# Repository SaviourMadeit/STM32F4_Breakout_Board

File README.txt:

# STM32F405RGT6_Breakout_Board

This repository contains the design files, schematics, and documentation for the STM32F4 Breakout Board.
This breakout board is designed to simplify the development process by providing easy access to essential 
features of the STM32F4 microcontroller, including voltage regulation, communication protocols, debugging interfaces, and indicator LEDs.

## Features

- 3.3V Voltage Regulator: The breakout board includes a 3.3V voltage regulator to ensure a stable power supply for 
                              connected peripherals and the STM32F4 microcontroller.

- 3.3V Power Pin: Provides a convenient 3.3V power pin for external components or modules that require a regulated power supply.

- LED Indicator: An indicator LED for visual feedback or status indication during development.

- Communication Protocols:

  - SPI: Headers and connectors for Serial Peripheral Interface (SPI) communication.
  - UART: Interface for Universal Asynchronous Receiver-Transmitter (UART) communication.
  - I2C: Connectors for Inter-Integrated Circuit (I2C) communication.

- Serial Wire Debugger Pins: Dedicated pins for Serial Wire Debugging (SWD) to assist in code development and debugging processes.

## Contents

- Schematics: Contains the schematic, and footprint files detailing the board's layout and connections.
- Gerber_Files: Gerber files for PCB fabrication and Assembly.
- Documentation: Additional documentation, usage guides, and pinout details.
- Examples: Sample code examples demonstrating the use of different communication protocols with the breakout board.

## Usage

1. Hardware Setup: Connect the necessary peripherals or components to the designated headers and pins on the breakout board.
   
2. Power Supply: Ensure a stable power supply of max 5v is provided to the breakout board through the appropriate power input VIN pin.

3. Communication: Utilize the provided headers and connectors to establish communication using SPI, UART, or I2C protocols.

4. Debugging: Utilize the Serial Wire Debugger pins for development and debugging of code. Refer to the documentation for more details on debugging setup.

## Contributing

Contributions to enhance the breakout board design, improve documentation, or add new features are welcome. 
Please follow the guidelines outlined in the `CONTRIBUTING.md` file.

## License

This project is licensed under the [MIT License](LICENSE).

## Acknowledgments

Special thanks to the Phil's Lab,STM32F4 community and contributors for their support and resources that aided in the development of this breakout board.

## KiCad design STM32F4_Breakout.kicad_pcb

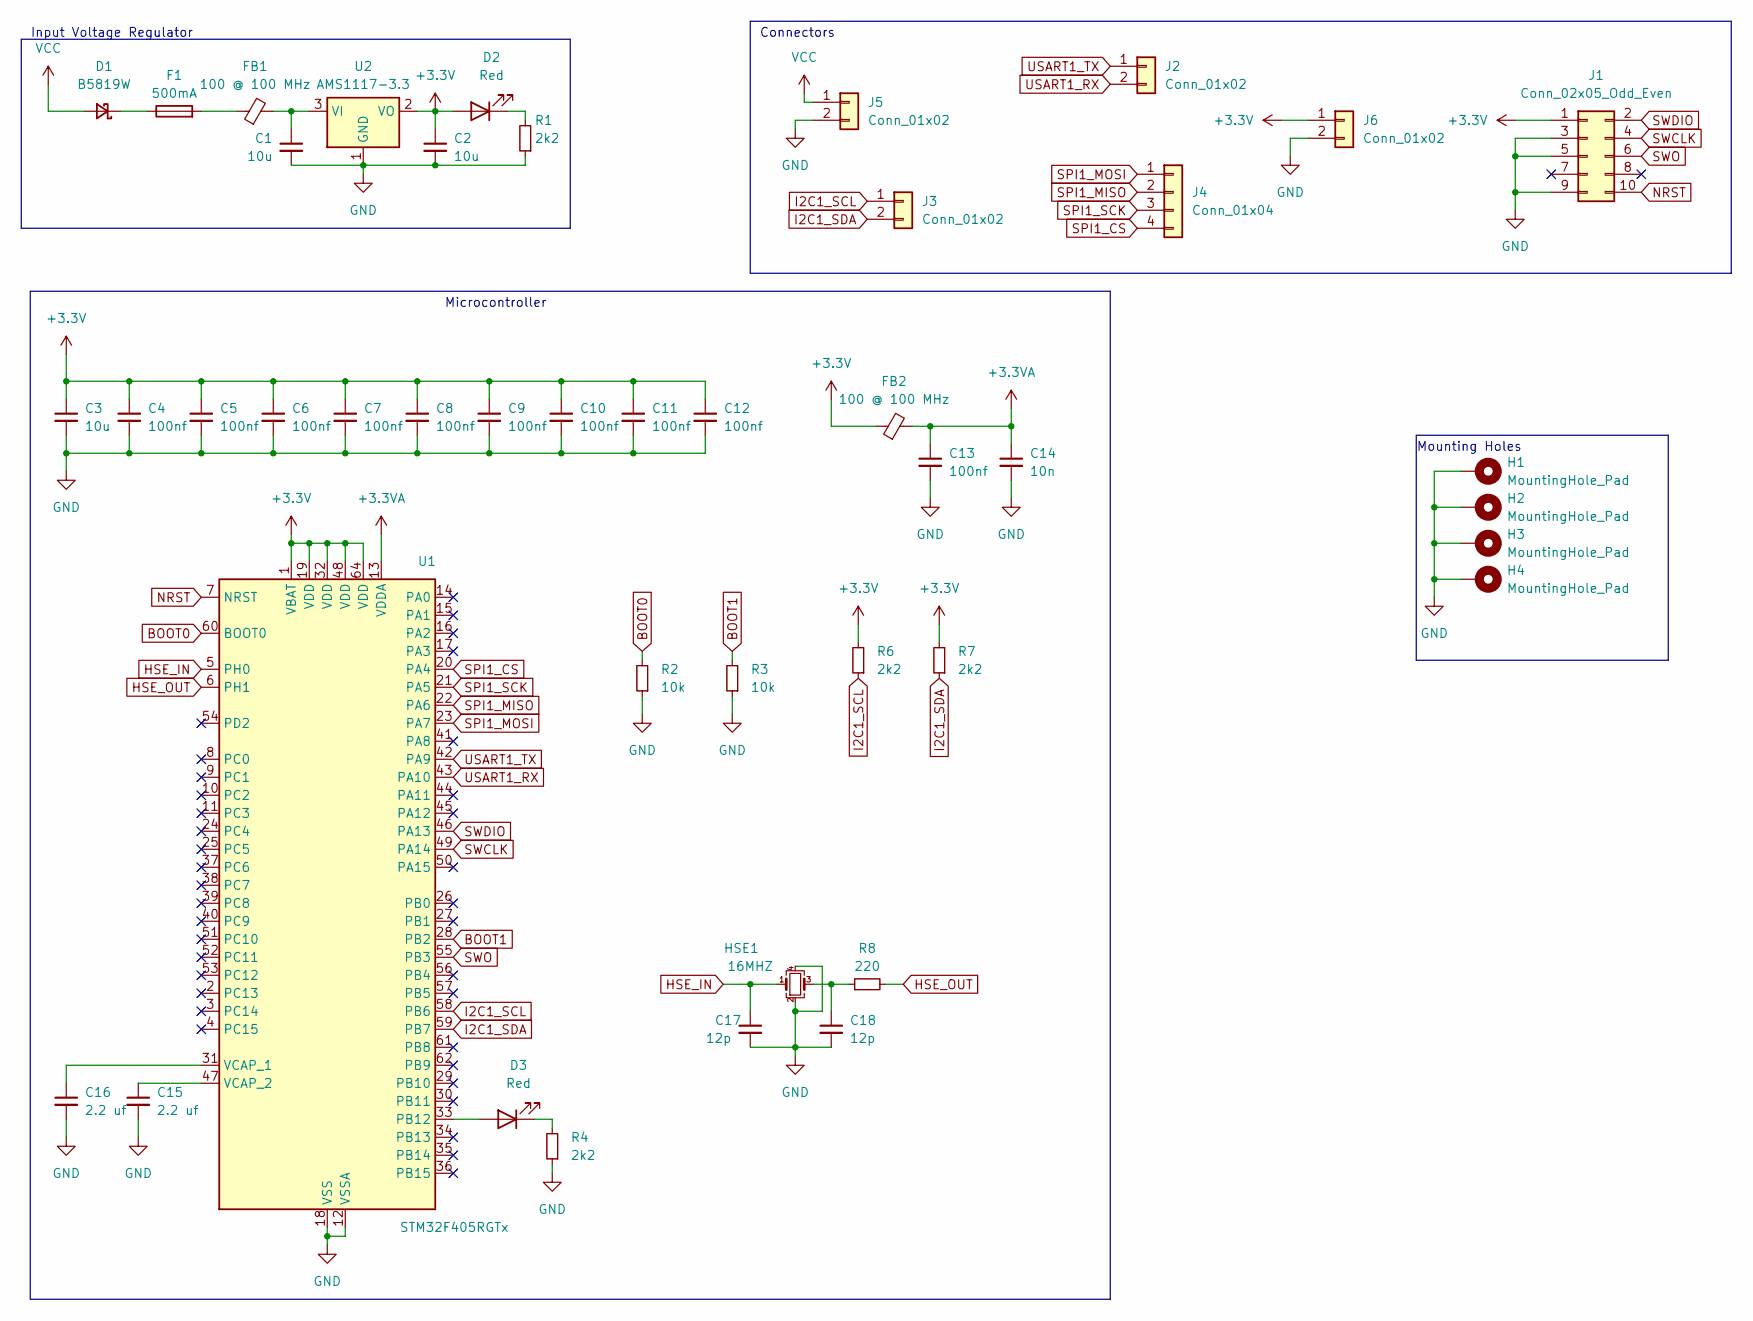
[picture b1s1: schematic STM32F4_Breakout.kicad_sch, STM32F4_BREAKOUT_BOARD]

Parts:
C1, C2: 10u; C_0805_2012Metric
C3: 10u; C_0603_1608Metric
C4, C5, C6, C7, C8, C9, C10, C11, C12, C13: 100nf; C_0402_1005Metric
C14: 10n; C_0402_1005Metric
C15, C16: 2.2 uf; C_0603_1608Metric
C17, C18: 12p; C_0402_1005Metric
D1: B5819W; D_SOD-123
D2, D3: Red; LED_0603_1608Metric
F1: 500mA; Fuse_0603_1608Metric
FB1, FB2: 100 @ 100 MHz; L_0805_2012Metric
H1, H2, H3, H4: MountingHole_Pad; MountingHole_4.3mm_M4_Pad_Via
HSE1: 16MHZ; Crystal_SMD_3225-4Pin_3.2x2.5mm
J1: Conn_02x05_Odd_Even; PinHeader_2x05_P2.54mm_Vertical_SMD
J2, J3, J5, J6: Conn_01x02; PinHeader_1x02_P2.54mm_Vertical
J4: Conn_01x04; PinHeader_1x04_P2.54mm_Vertical
R1, R4: 2k2; R_0603_1608Metric
R2, R3: 10k; R_0402_1005Metric
R6, R7: 2k2; R_0402_1005Metric
R8: 220; R_0402_1005Metric
U1: STM32F405RGTx; LQFP-64_10x10mm_P0.5mm
U2: AMS1117-3.3; SOT-223-3_TabPin2

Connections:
+3.3V: C2.1, C3.1, C4.1, C5.1, C6.1, C7.1, C8.1, C9.1, C10.1, C11.1, C12.1, D2.2 (A), FB2.1, J1.1, J6.1, R6.2, R7.2, U1.1 (VBAT), U1.19 (VDD), U1.32 (VDD), U1.48 (VDD), U1.64 (VDD), U2.2 (VO)
+3.3VA: C13.1, C14.1, FB2.2, U1.13 (VDDA)
BOOT0: R2.2, U1.60 (BOOT0)
BOOT1: R3.2, U1.28 (PB2)
GND: C1.2, C2.2, C3.2, C4.2, C5.2, C6.2, C7.2, C8.2, C9.2, C10.2, C11.2, C12.2, C13.2, C14.2, C15.2, C16.2, C17.2, C18.2, H1.1, H2.1, H3.1, H4.1, HSE1.2, HSE1.4, J1.3, J1.5, J1.9, J5.2, J6.2, R1.1, R2.1, R3.1, R4.1, U1.12 (VSSA), U1.18 (VSS), U1.63 (VSS), U2.1 (GND)
HSE_IN: C17.1, HSE1.1, U1.5 (PH0)
HSE_OUT: R8.2, U1.6 (PH1)
I2C1_SCL: J3.1, R6.1, U1.58 (PB6)
I2C1_SDA: J3.2, R7.1, U1.59 (PB7)
NRST: J1.10, U1.7 (NRST)
unnamed: C18.1, HSE1.3, R8.1
unnamed: D1.1 (K), F1.1
unnamed: D2.1 (K), R1.2
unnamed: D3.2 (A), U1.33 (PB12)
unnamed: D3.1 (K), R4.2
unnamed: F1.2, FB1.1
unnamed: C16.1, U1.31 (VCAP_1)
unnamed: C15.1, U1.47 (VCAP_2)
unnamed: C1.1, FB1.2, U2.3 (VI)
SPI1_CS: J4.4, U1.20 (PA4)
SPI1_MISO: J4.2, U1.22 (PA6)
SPI1_MOSI: J4.1, U1.23 (PA7)
SPI1_SCK: J4.3, U1.21 (PA5)
SWCLK: J1.4, U1.49 (PA14)
SWDIO: J1.2, U1.46 (PA13)
SWO: J1.6, U1.55 (PB3)
USART1_RX: J2.2, U1.43 (PA10)
USART1_TX: J2.1, U1.42 (PA9)
VCC: D1.2 (A), J5.1

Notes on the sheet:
Microcontroller
Mounting Holes
Input Voltage Regulator
Connectors

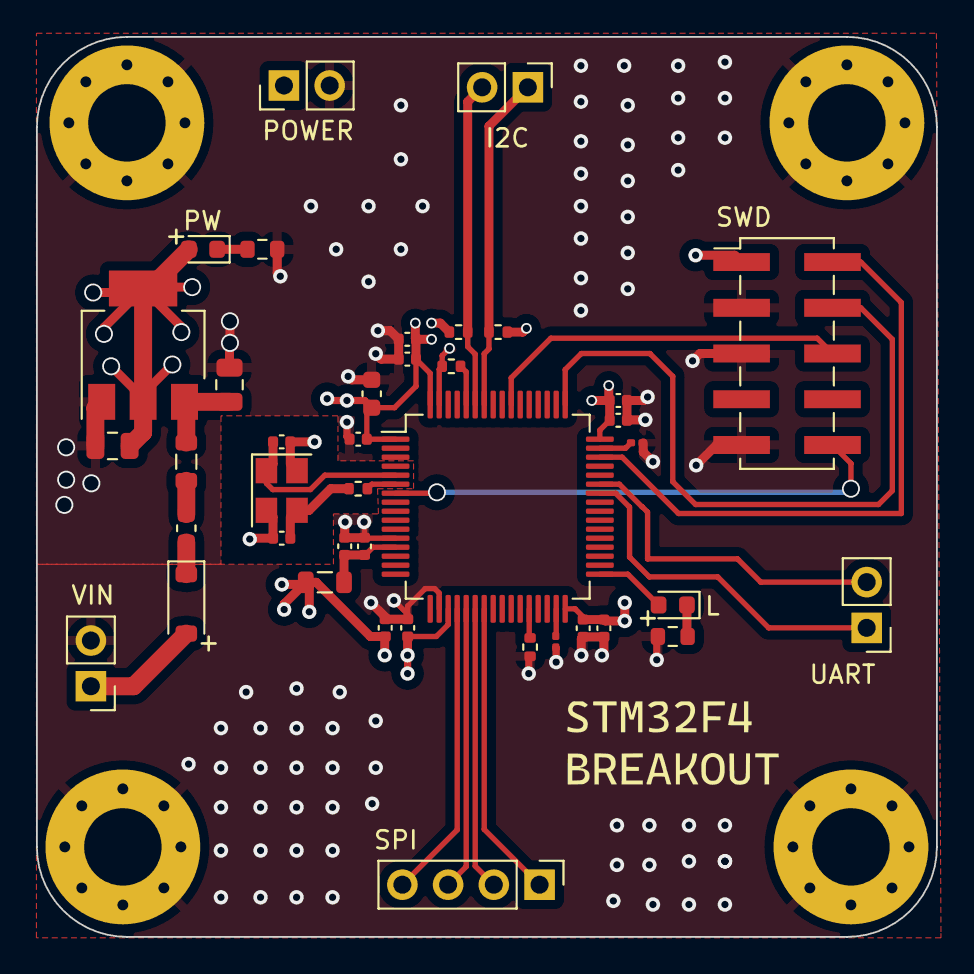
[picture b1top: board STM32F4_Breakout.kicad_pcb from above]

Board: 4 copper layers, 50.0 x 50.0 mm, 44 parts (0 on the bottom side), 29 nets.
